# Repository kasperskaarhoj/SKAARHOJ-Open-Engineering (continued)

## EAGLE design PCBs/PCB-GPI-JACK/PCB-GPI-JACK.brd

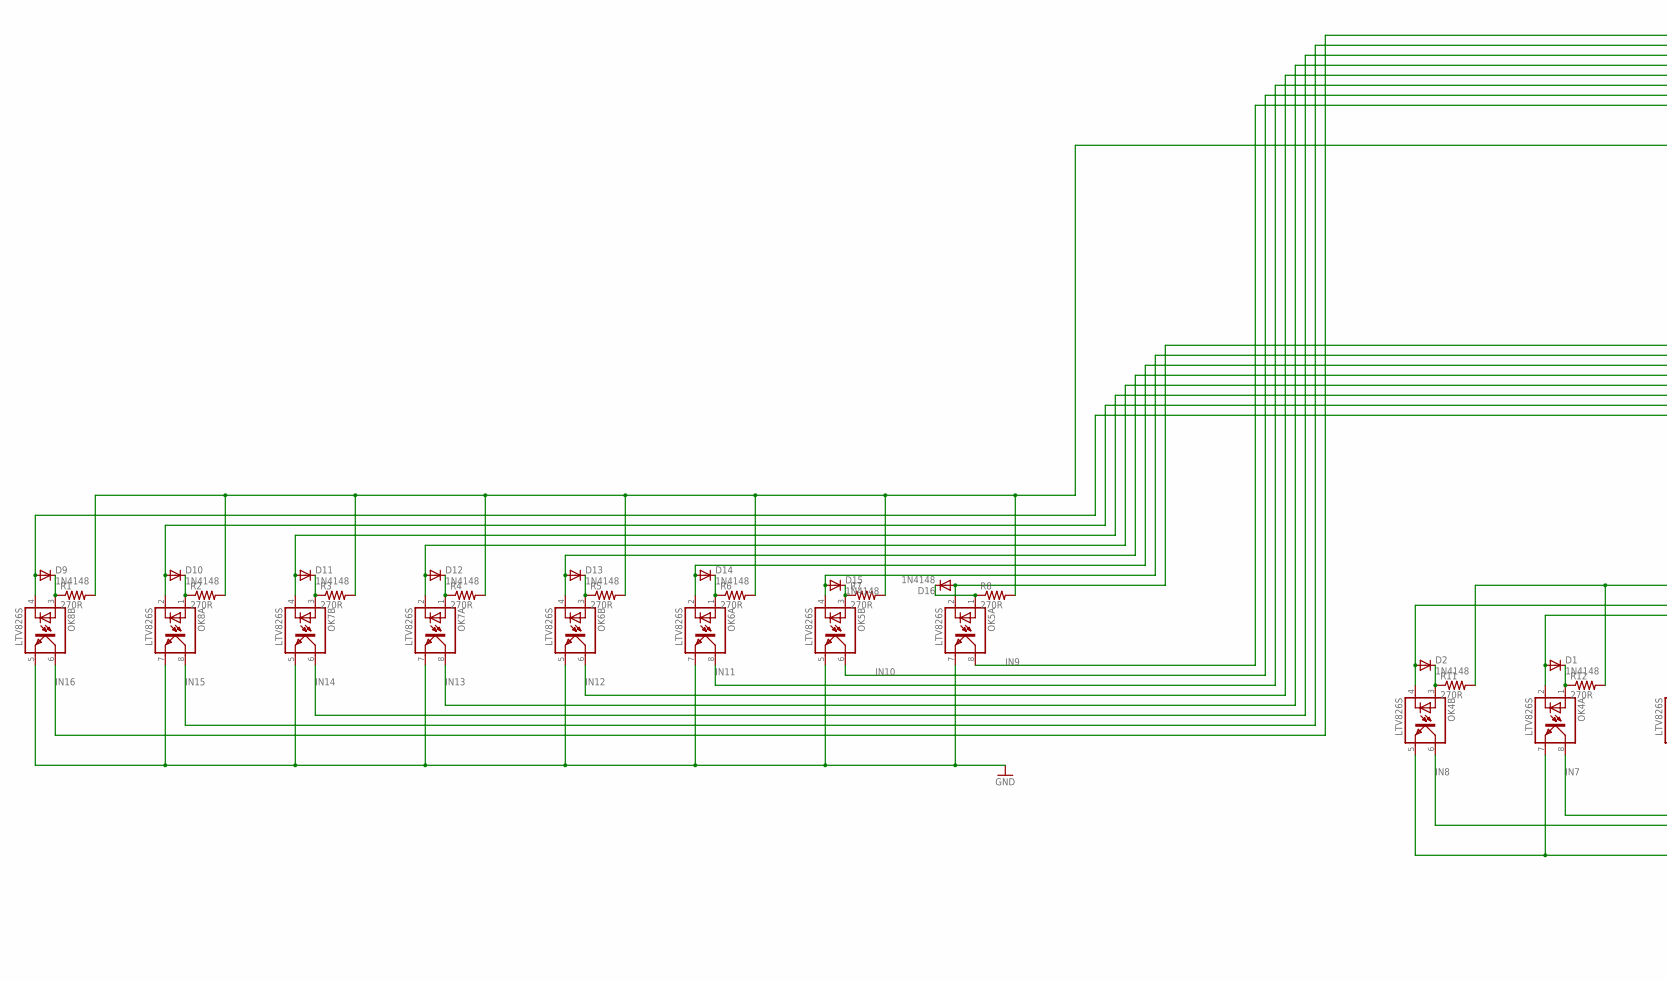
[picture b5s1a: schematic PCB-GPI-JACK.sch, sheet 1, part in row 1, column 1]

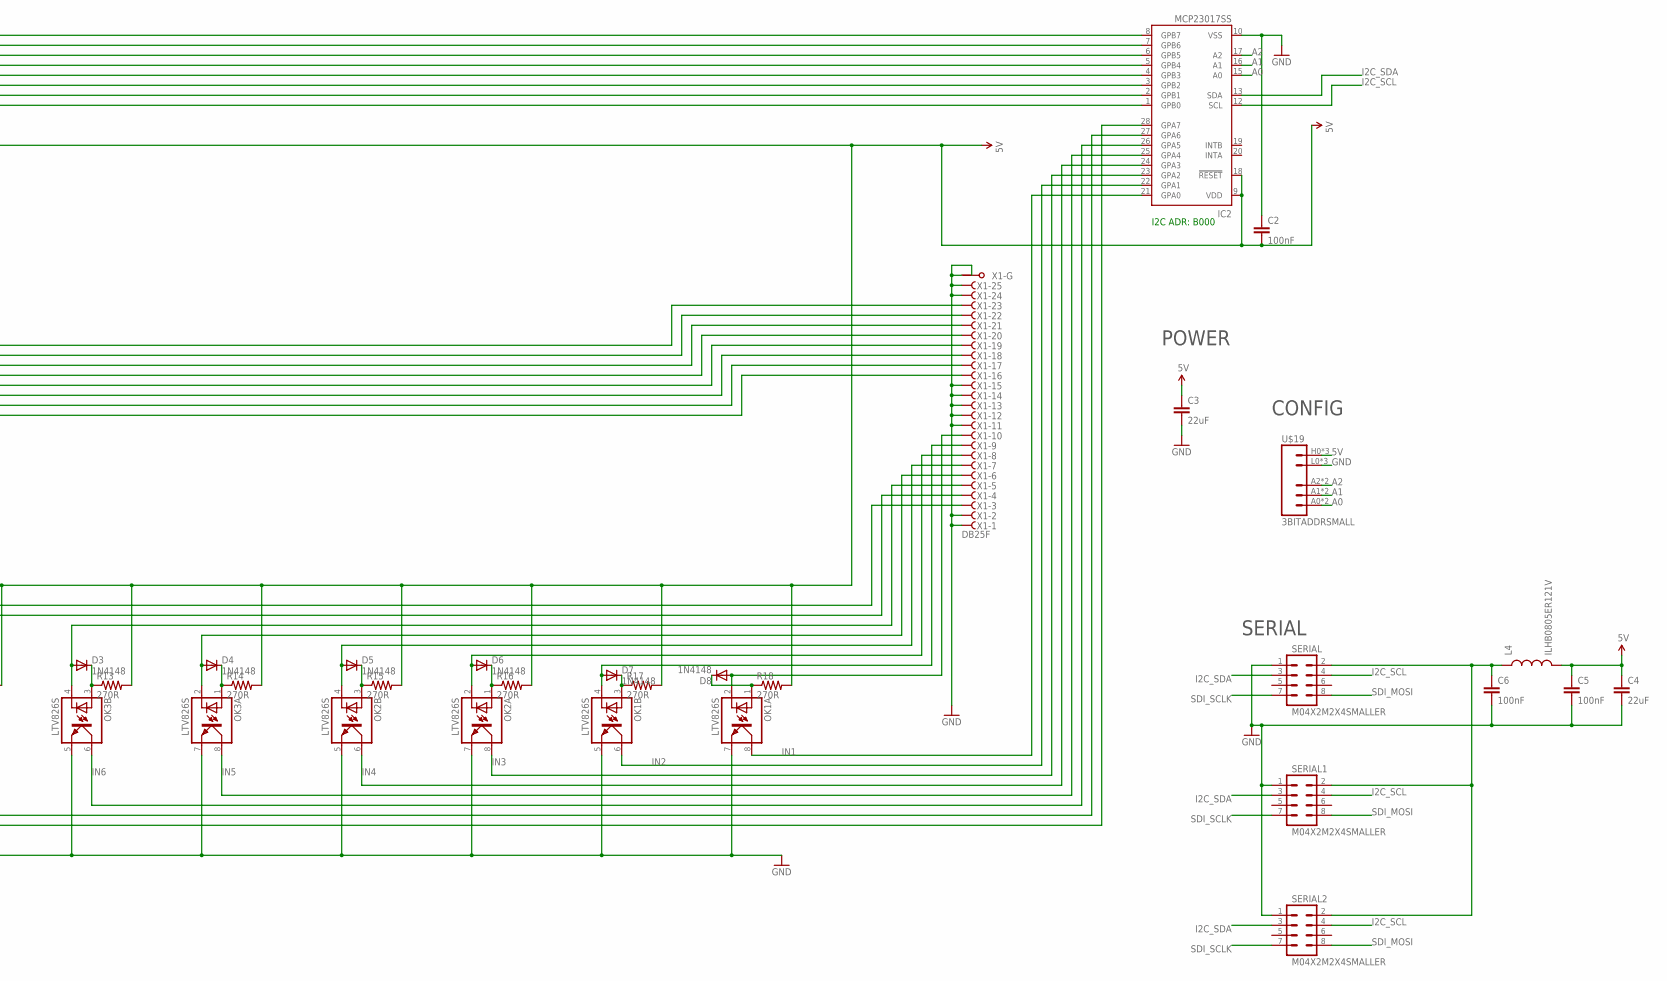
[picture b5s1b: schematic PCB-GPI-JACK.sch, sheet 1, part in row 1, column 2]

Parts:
C2, C5, C6: 100nF; 0603-CAP
C3, C4: 22uF; 0805
D1, D2, D3, D4, D5, D6, D7, D8, D9, D10, D11, D12, D13, D14, D15, D16: 1N4148; SOD-323
IC2: MCP23017SS; SSOP28
L4: ILHB0805ER121V; 0805
OK1, OK2, OK3, OK4, OK5, OK6, OK7, OK8: LTV826S; DIL8-SMD
R1, R2, R3, R4, R5, R6, R7, R8, R11, R12, R13, R14, R15, R16, R17, R18: 270R; 0603-RES
SERIAL, SERIAL1, SERIAL2: M04X2M2X4SMALLER; M2X4SMALLER
U$19: 3BITADDRSMALL; 3BITADDR_SMALL
X1: DB25F; F25HP

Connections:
5V: C2.2, C3.1, C4.1, C5.1, IC2.9 (VDD), IC2.18 (!RESET), L4.2, R1.2, R2.2, R3.2, R4.2, R5.2, R6.2, R7.2, R8.2, R11.2, R12.2, R13.2, R14.2, R15.2, R16.2, R17.2, R18.2, U$19.H0 (VCC), U$19.H1 (VCC), U$19.H2 (VCC)
A0: IC2.15 (A0), U$19.A0, U$19.AS0 (A0)
A1: IC2.16 (A1), U$19.A1, U$19.AS1 (A1)
A2: IC2.17 (A2), U$19.A2, U$19.AS2 (A2)
GND: C2.1, C3.2, C4.2, C5.2, C6.2, IC2.10 (VSS), OK1.5 (EMIT), OK1.7 (EMIT), OK2.5 (EMIT), OK2.7 (EMIT), OK3.5 (EMIT), OK3.7 (EMIT), OK4.5 (EMIT), OK4.7 (EMIT), OK5.5 (EMIT), OK5.7 (EMIT), OK6.5 (EMIT), OK6.7 (EMIT), OK7.5 (EMIT), OK7.7 (EMIT), OK8.5 (EMIT), OK8.7 (EMIT), SERIAL.1, SERIAL1.1, SERIAL2.1, U$19.L0 (GND), U$19.L1 (GND), U$19.L2 (GND), X1.1 (F), X1.2 (F), X1.11 (F), X1.12 (F), X1.13 (F), X1.14 (F), X1.15 (F), X1.24 (F), X1.25 (F), X1.G1, X1.G2
I2C_SCL: IC2.12 (SCL), SERIAL.4, SERIAL1.4, SERIAL2.4
I2C_SDA: IC2.13 (SDA), SERIAL.3, SERIAL1.3, SERIAL2.3
IN1: IC2.21 (GPA0), OK1.8 (COL)
IN2: IC2.22 (GPA1), OK1.6 (COL)
IN3: IC2.23 (GPA2), OK2.8 (COL)
IN4: IC2.24 (GPA3), OK2.6 (COL)
IN5: IC2.25 (GPA4), OK3.8 (COL)
IN6: IC2.26 (GPA5), OK3.6 (COL)
IN7: IC2.27 (GPA6), OK4.8 (COL)
IN8: IC2.28 (GPA7), OK4.6 (COL)
IN9: IC2.1 (GPB0), OK5.8 (COL)
IN10: IC2.2 (GPB1), OK5.6 (COL)
IN11: IC2.3 (GPB2), OK6.8 (COL)
IN12: IC2.4 (GPB3), OK6.6 (COL)
IN13: IC2.5 (GPB4), OK7.8 (COL)
IN14: IC2.6 (GPB5), OK7.6 (COL)
IN15: IC2.7 (GPB6), OK8.8 (COL)
IN16: IC2.8 (GPB7), OK8.6 (COL)
unnamed: D16.2 (A), OK5.2 (C), X1.23 (F)
unnamed: C6.1, L4.1, SERIAL.2, SERIAL1.2, SERIAL2.2
unnamed: D12.2 (A), OK7.2 (C), X1.19 (F)
unnamed: D15.2 (A), OK5.4 (C), X1.22 (F)
unnamed: D14.2 (A), OK6.2 (C), X1.21 (F)
unnamed: D13.2 (A), OK6.4 (C), X1.20 (F)
unnamed: D11.2 (A), OK7.4 (C), X1.18 (F)
unnamed: D10.2 (A), OK8.2 (C), X1.17 (F)
unnamed: D9.2 (A), OK8.4 (C), X1.16 (F)
unnamed: D9.1 (C), OK8.3 (A), R1.1
unnamed: D2.1 (C), OK4.3 (A), R11.1
unnamed: D10.1 (C), OK8.1 (A), R2.1
unnamed: D1.1 (C), OK4.1 (A), R12.1
unnamed: D3.1 (C), OK3.3 (A), R13.1
unnamed: D4.1 (C), OK3.1 (A), R14.1
unnamed: D11.1 (C), OK7.3 (A), R3.1
unnamed: D5.1 (C), OK2.3 (A), R15.1
unnamed: D6.1 (C), OK2.1 (A), R16.1
unnamed: D7.1 (C), OK1.3 (A), R17.1
unnamed: D12.1 (C), OK7.1 (A), R4.1
unnamed: D8.1 (C), OK1.1 (A), R18.1
unnamed: D13.1 (C), OK6.3 (A), R5.1
unnamed: D14.1 (C), OK6.1 (A), R6.1
unnamed: D15.1 (C), OK5.3 (A), R7.1
unnamed: D16.1 (C), OK5.1 (A), R8.1
unnamed: D8.2 (A), OK1.2 (C), X1.10 (F)
unnamed: D4.2 (A), OK3.2 (C), X1.6 (F)
unnamed: D7.2 (A), OK1.4 (C), X1.9 (F)
unnamed: D6.2 (A), OK2.2 (C), X1.8 (F)
unnamed: D5.2 (A), OK2.4 (C), X1.7 (F)
unnamed: D3.2 (A), OK3.4 (C), X1.5 (F)
unnamed: D1.2 (A), OK4.2 (C), X1.4 (F)
unnamed: D2.2 (A), OK4.4 (C), X1.3 (F)
SDI_MOSI: SERIAL.8, SERIAL1.8, SERIAL2.8
SDI_SCLK: SERIAL.7, SERIAL1.7, SERIAL2.7

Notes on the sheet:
I2C ADR: B000
SERIAL
POWER
CONFIG

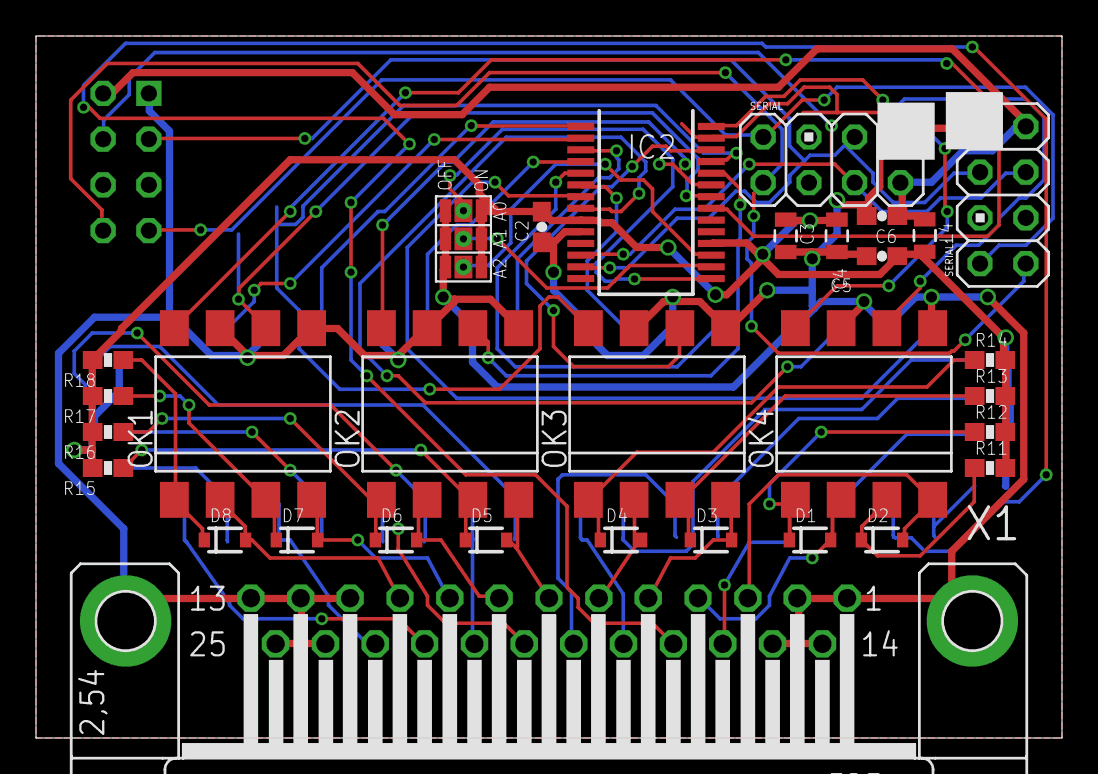
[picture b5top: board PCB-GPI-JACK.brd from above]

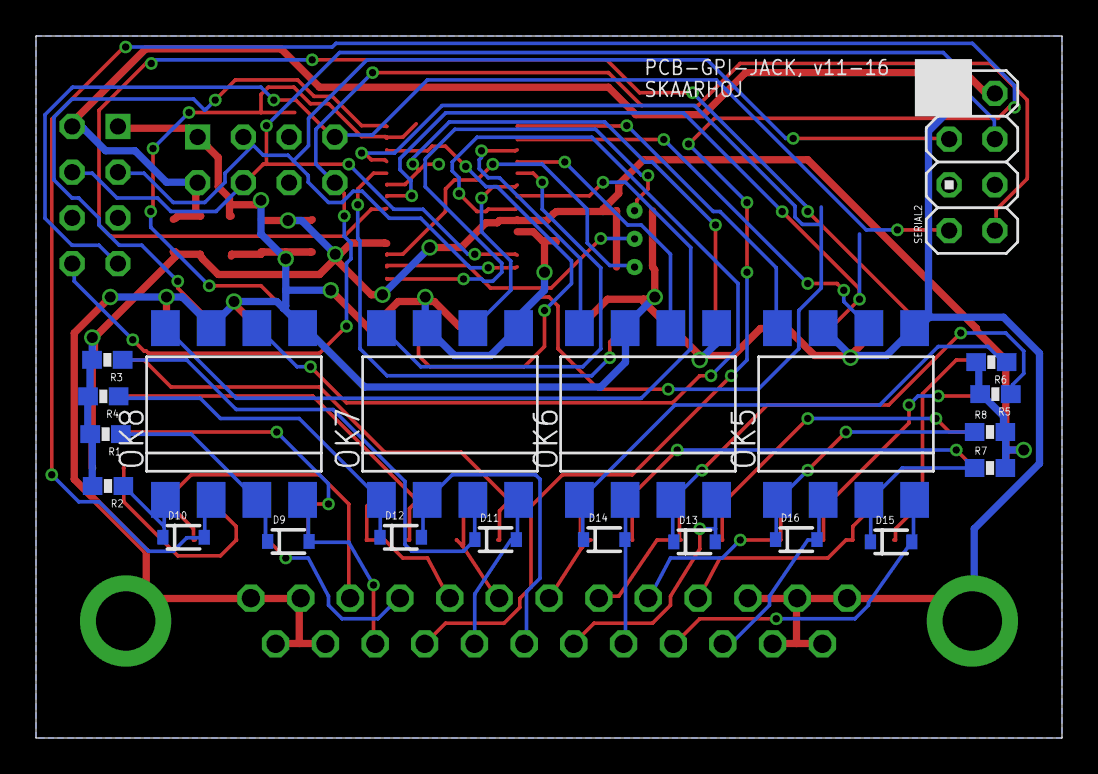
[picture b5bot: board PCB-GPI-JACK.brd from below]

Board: 2 copper layers, 57.0 x 39.0 mm, 52 parts (21 on the bottom side), 58 nets.

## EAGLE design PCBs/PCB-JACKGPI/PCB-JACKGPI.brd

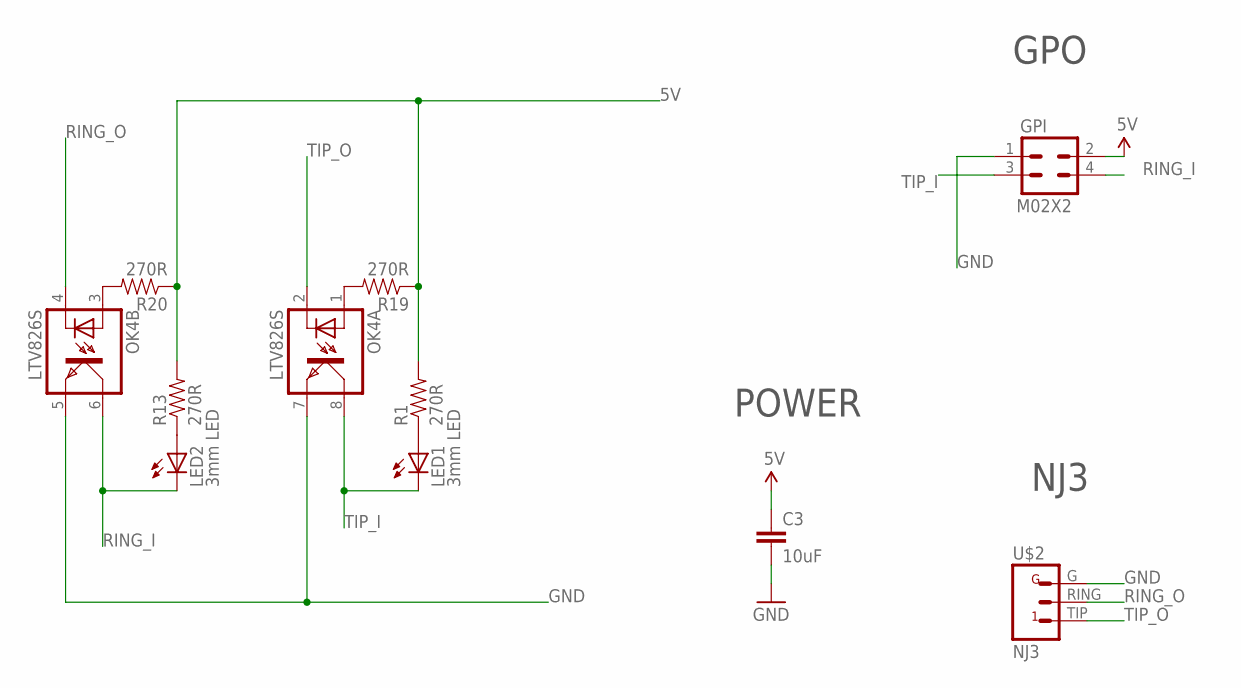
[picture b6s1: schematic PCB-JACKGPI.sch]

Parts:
C3: 10uF; 0805
GPI: M02X2; 2X2
LED1, LED2: 3mm LED; LED3MM
OK4: LTV826S; DIL8-SMD
R1, R13, R19, R20: 270R; 0603-RES
U$2: NJ3; NJ3FP6C

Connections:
5V: C3.1, GPI.2, R1.2, R13.2, R19.1, R20.1
GND: C3.2, GPI.1, OK4.5 (EMIT), OK4.7 (EMIT), U$2.G
unnamed: LED1.A, R1.1
unnamed: LED2.A, R13.1
unnamed: OK4.1 (A), R19.2
unnamed: OK4.3 (A), R20.2
RING_I: GPI.4, LED2.K (C), OK4.6 (COL)
RING_O: OK4.4 (C), U$2.RING (2)
TIP_I: GPI.3, LED1.K (C), OK4.8 (COL)
TIP_O: OK4.2 (C), U$2.TIP (1)

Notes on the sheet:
NJ3
GPO
POWER

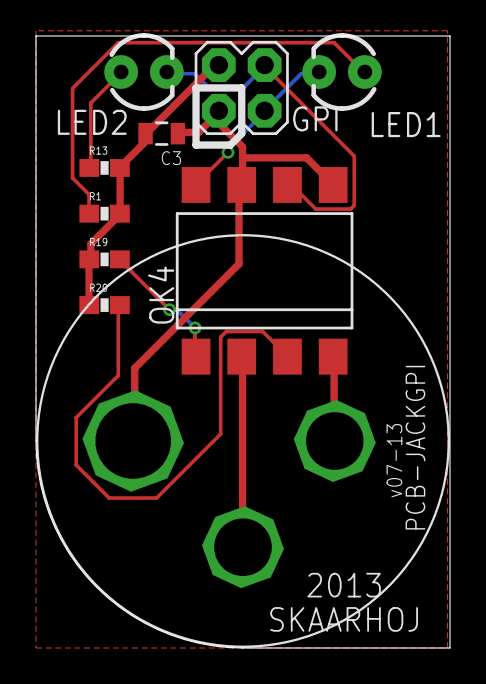
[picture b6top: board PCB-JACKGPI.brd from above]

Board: 2 copper layers, 23.0 x 34.0 mm, 10 parts (0 on the bottom side), 10 nets.

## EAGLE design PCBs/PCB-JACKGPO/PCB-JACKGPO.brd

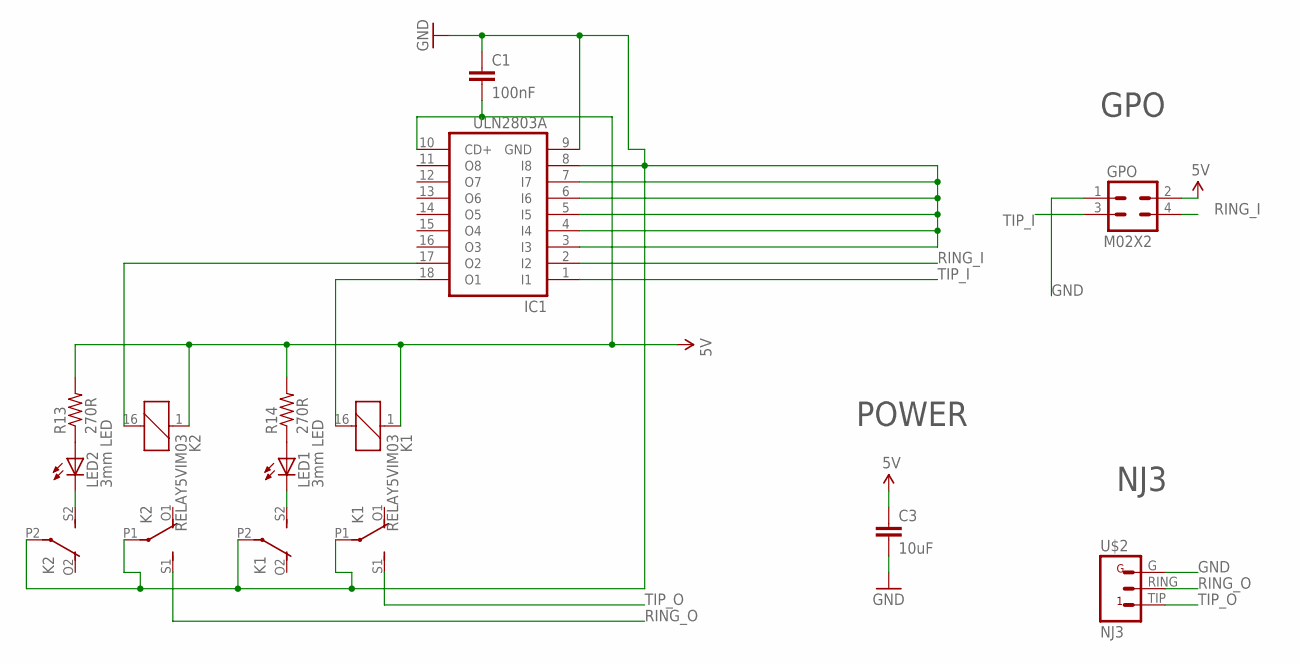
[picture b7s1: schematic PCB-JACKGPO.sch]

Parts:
C1: 100nF; 0805
C3: 10uF; 0805
GPO: M02X2; 2X2
IC1: ULN2803A; SO18W
K1, K2: RELAY5VIM03; DS2Y
LED1, LED2: 3mm LED; LED3MM
R13, R14: 270R; 0603-RES
U$2: NJ3; NJ3FP6C

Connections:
5V: C1.2, C3.1, GPO.2, IC1.10 (CD+), K1.1, K2.1, R13.2, R14.2
GND: C1.1, C3.2, GPO.1, IC1.3 (I3), IC1.4 (I4), IC1.5 (I5), IC1.6 (I6), IC1.7 (I7), IC1.8 (I8), IC1.9 (GND), K1.P1, K1.P2, K2.P1, K2.P2, U$2.G
unnamed: K1.S2 (S), LED1.K (C)
unnamed: IC1.18 (O1), K1.16 (2)
unnamed: K2.S2 (S), LED2.K (C)
unnamed: IC1.17 (O2), K2.16 (2)
unnamed: LED2.A, R13.1
unnamed: LED1.A, R14.1
RING_I: GPO.4, IC1.2 (I2)
RING_O: K2.S1 (S), U$2.RING (2)
TIP_I: GPO.3, IC1.1 (I1)
TIP_O: K1.S1 (S), U$2.TIP (1)

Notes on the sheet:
NJ3
GPO
POWER

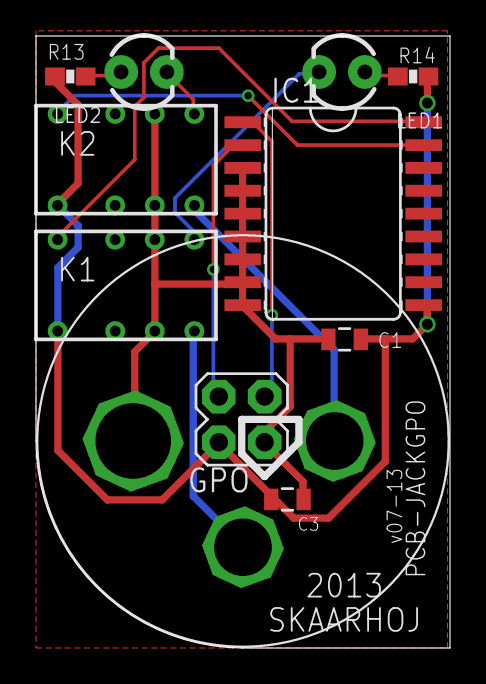
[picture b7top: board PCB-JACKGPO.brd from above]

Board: 2 copper layers, 23.0 x 34.0 mm, 11 parts (0 on the bottom side), 12 nets.
